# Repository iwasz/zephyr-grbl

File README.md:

# What this is
A GRBL ported to Zephyr RTOS with some additional features like software CDC ACM serial port and SD card support. Developed for my CoreXY pen ploter, so some features of GRBL are commented out. Please create an issue or propose a pull request if you are interested in more functionality (list of unsupported bits is below). The greatest benefit of having the GRBL ported to Zephyr is the ability of running it on variety of platforms with way more powerful CPUs than the original Arduino. As of now this project is targeting the [STM32F405RG](https://www.st.com/en/microcontrollers-microprocessors/stm32f405rg.html) (earlier tests were performed on the [STM32F446RE](https://www.st.com/en/microcontrollers-microprocessors/stm32f446re.html)) and with minor modifications in the *boards* directory or *overlay* file (or adding either of those to be precise) it should work on different STM32-s as well.

The only *non standard* driver this project uses is the `modules/hw_timer` and this is the only obstacle for running this on MCUs different than STM32-s. `modules/hw_timer` is derived from the `pwm` driver and its only purpose is to fire a callback(s) on a timer update event (and possibly on output compare event in the future). Other parts are implemented in stock Zephyr.

The project was written to power my [CoreXY pen plotter](https://hackaday.io/project/177237-corexy-pen-plotter), and as such has some parts not implemented (probing) and others not tested (Z-axis with stepper motor, see below). It should be a good starting point to develop something more complete that would run the variety of CNC machines. Pull requests are welcome.

* [TODO](TODO.md) list of things to do.
* [My notes](NOTES.md) on problems I've had.
* [Hackaday.io project page](https://hackaday.io/project/177237-corexy-pen-plotter)

# How to build
Tested with Zephyr RTOS 2.6.99. Familiarize yourself with the [Zephyr RTOS build process](https://docs.zephyrproject.org/latest/getting_started/index.html) first. :

## With bootloader
?

## Without bootloader (only for troubleshooting)
That is when `CONFIG_BOOTLOADER_MCUBOOT=n` in the `prj.conf`.
```sh
rm -Rf build
cmake -B build -GNinja -DBOARD=plotter_f405rg -DBOARD_ROOT=. .
ninja -C build
west flash # Or use IDE, or use openocd directly
```

## What has been done in order to port GRBL
* Added a new macro for my machine named DEFAULTS_ZEPHYR_GRBL_PLOTTER in the `config.h` and globally in the `CMakeLists.txt`. Used mostly in the `defaults.h`
* Coolant control, spindle **comented out**.
* [x] Added `extern "C" {` to most of the `*.h` files to enable C++ interoperability.
* [x] Added definitions for my machine in the `defaults.h`.
* [ ] Eeprom support ported.
* [x] Zephyr PWM module was modified to accept a timer output compare ISR callback.
* [x] AVR GPIO registers code ported to zephyr
* [x] Homing and limiters ported.
* [x] Probe implementation commented out.
* [x] Control switches support commented out. I'll have an OLED display and I can add those features there.
* [x] Spindle control commented out.
* [x] ~~Gpio inverting functionality stripped down as from now the Zephyr's device tree configuration is used for this.~~
* ~~Logging ported to Zephyr.~~ Rolled back.
* [x] Port uart code to zephyr.
  * [ ] ~~Make use of new async uart functionality merged recently to zephyr.~~ [Analogous to this](https://github.com/zephyrproject-rtos/zephyr/pull/30917/commits/a62711bd260fea80948f668d35b05452bd26e95f).
    * [x] ~~Modify the overlay.~~
    * [x] ~~Turn DMA on in Kconfig.~~
    * [x] Interrupt UART API and Zephyr ring buffers.
* GRBL seems to lack any call to a `delay` function in the main loop. This prevents scheduler from switching to other lower-priority threads which in my case were : `idle`, `logging` and `shell_uart`. I've lowered the main thread priority to 14 (from 0) and added k_yeld, so other low priority threads have a chance to run now. This include logging, shell and others.
-----
-----
-----

# Topics to mention in a write up
* Software
  * Out of tree driver for timer callback.
  * TMC driver?
  * GRBL obviously.

## Driver
Derived from PWM driver. Changes:

Header:
* Names (file names & all the names in the code). PWM -> HW_TIMER.
* A `typedef` for the callback.
* Few macro / defines.

Source file:
* Names
* Callback setter
* Datadield for the callback.
* TODO remove unused code.

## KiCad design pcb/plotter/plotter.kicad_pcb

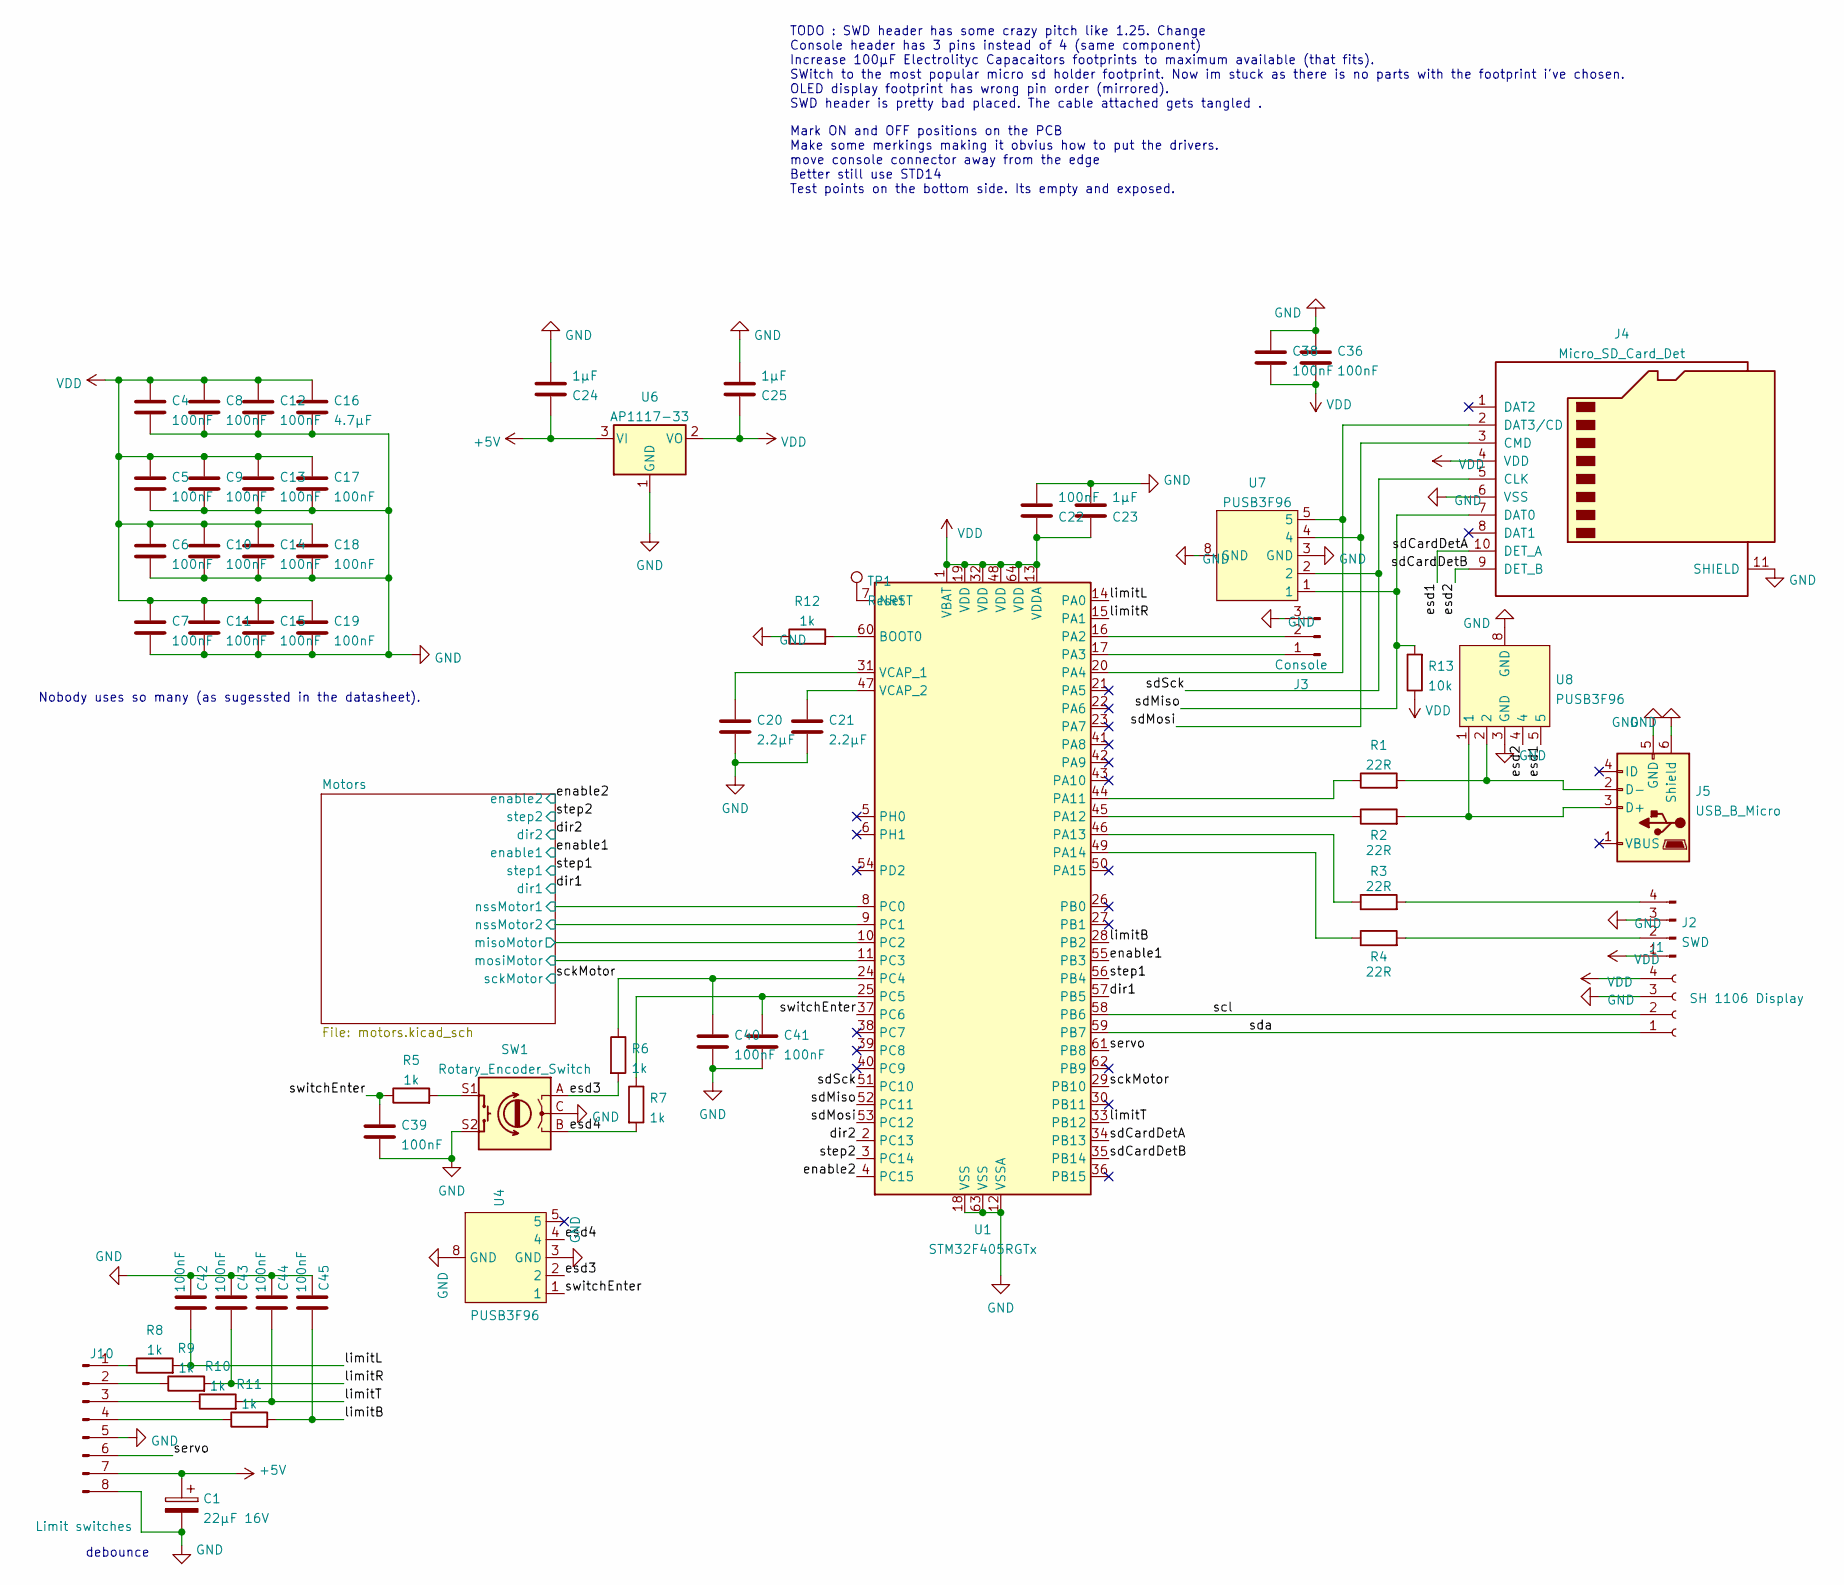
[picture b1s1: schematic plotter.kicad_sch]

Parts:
C1: 22µF 16V; CP_Elec_8x10
C4, C5, C6, C7, C8, C9, C10, C11, C12, C13, C14, C15, C17, C18, C19, C22, C36, C38, C39, C40, C41, C42, C43, C44, C45: 100nF; C_0603_1608Metric
C16: 4.7µF; C_1210_3225Metric
C20, C21: 2.2µF; C_1206_3216Metric
C23, C24, C25: 1µF; C_0603_1608Metric
J1: SH 1106 Display; SH1106
J2: SWD; PinHeader_1x04_P1.27mm_Vertical
J3: Console; PinHeader_1x03_P1.27mm_Vertical
J4: Micro_SD_Card_Det; microSD_HC_Hirose_DM3AT-SF-PEJM5
J5: USB_B_Micro; USB_Micro-B_Amphenol_10104110_Horizontal
J10: Limit switches; JST_PH_B8B-PH-K_1x08_P2.00mm_Vertical
R1, R2, R3, R4: 22R; R_0603_1608Metric
R5, R6, R7, R8, R9, R10, R11, R12: 1k; R_0603_1608Metric
R13: 10k; R_0603_1608Metric
SW1: Rotary_Encoder_Switch; RotaryEncoder_Alps_EC11E_Vertical_H20mm
TP1: Reset; TestPoint_Pad_1.5x1.5mm
U1: STM32F405RGTx; LQFP-64_10x10mm_P0.5mm
U4, U7, U8: PUSB3F96; Diodes_UDFN-10_1.0x2.5mm_P0.5mm
U6: AP1117-33; SOT-223-3_TabPin2

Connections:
+5V: C1.1, C24.1, J10.7, U6.3 (VI); also elsewhere on the board
/Motors/misoMotor: U1.10 (PC2); also elsewhere on the board
/Motors/mosiMotor: U1.11 (PC3); also elsewhere on the board
/Motors/nssMotor1: U1.8 (PC0); also elsewhere on the board
/Motors/nssMotor2: U1.9 (PC1); also elsewhere on the board
/dir1: U1.57 (PB5); also elsewhere on the board
/dir2: U1.2 (PC13); also elsewhere on the board
/enable1: U1.55 (PB3); also elsewhere on the board
/enable2: U1.4 (PC15); also elsewhere on the board
/esd1: J4.10 (DET_A), U1.34 (PB13), U8.5
/esd2: J4.9 (DET_B), U1.35 (PB14), U8.4
/esd3: R6.2, SW1.A, U4.2
/esd4: R7.2, SW1.B, U4.4
/limitB: C45.2, R11.2, U1.28 (PB2)
/limitL: C42.2, R8.2, U1.14 (PA0)
/limitR: C43.2, R9.2, U1.15 (PA1)
/limitT: C44.2, R10.2, U1.33 (PB12)
/sckMotor: U1.29 (PB10); also elsewhere on the board
/scl: J1.2, U1.58 (PB6)
/sdMiso: J4.7 (DAT0), R13.2, U1.52 (PC11), U7.1
/sdMosi: J4.3 (CMD), U1.53 (PC12), U7.4
/sdSck: J4.5 (CLK), U1.51 (PC10), U7.2
/sda: J1.1, U1.59 (PB7)
/servo: J10.6, U1.61 (PB8)
/step1: U1.56 (PB4); also elsewhere on the board
/step2: U1.3 (PC14); also elsewhere on the board
/switchEnter: C39.1, R5.1, U1.37 (PC6), U4.1
GND: C1.2, C4.2, C5.2, C6.2, C7.2, C8.2, C9.2, C10.2, C11.2, C12.2, C13.2, C14.2, C15.2, C16.2, C17.2, C18.2, C19.2, C20.2, C21.2, C22.2, C23.2, C24.2, C25.2, C36.1, C38.1, C39.2, C40.2, C41.2, C42.1, C43.1, C44.1, C45.1, J1.3, J2.3, J3.3, J4.6 (VSS), J4.11 (SHIELD), J5.5 (GND), J5.6 (Shield), J10.5, J10.8, R12.1, SW1.C, SW1.S2, U1.12 (VSSA), U1.18 (VSS), U1.63 (VSS), U4.3 (GND), U4.8 (GND), U6.1 (GND), U7.3 (GND), U7.8 (GND), U8.3 (GND), U8.8 (GND); also elsewhere on the board
unnamed: C20.1, U1.31 (VCAP_1)
unnamed: C21.1, U1.47 (VCAP_2)
unnamed: C40.1, R6.1, U1.24 (PC4)
unnamed: C41.1, R7.1, U1.25 (PC5)
unnamed: J2.2, R4.2
unnamed: J2.4, R3.2
unnamed: J3.1, U1.17 (PA3)
unnamed: J3.2, U1.16 (PA2)
unnamed: J4.2 (DAT3/CD), U1.20 (PA4), U7.5
unnamed: J5.2 (D-), R1.2, U8.2
unnamed: J5.3 (D+), R2.2, U8.1
unnamed: J10.1, R8.1
unnamed: J10.2, R9.1
unnamed: J10.3, R10.1
unnamed: J10.4, R11.1
unnamed: R1.1, U1.44 (PA11)
unnamed: R2.1, U1.45 (PA12)
unnamed: R3.1, U1.46 (PA13)
unnamed: R4.1, U1.49 (PA14)
unnamed: R5.2, SW1.S1
unnamed: R12.2, U1.60 (BOOT0)
unnamed: TP1.1, U1.7 (NRST)
VDD: C4.1, C5.1, C6.1, C7.1, C8.1, C9.1, C10.1, C11.1, C12.1, C13.1, C14.1, C15.1, C16.1, C17.1, C18.1, C19.1, C22.1, C23.1, C25.1, C36.2, C38.2, J1.4, J2.1, J4.4 (VDD), R13.1, U1.1 (VBAT), U1.13 (VDDA), U1.19 (VDD), U1.32 (VDD), U1.48 (VDD), U1.64 (VDD), U6.2 (VO)

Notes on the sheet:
Nobody uses so many (as sugessted in the datasheet).
TODO : SWD header has some crazy pitch like 1.25. Change Console header has 3 pins instead of 4 (same component) Increase 100µF Electrolityc Capacaitors footprints to maximum available (that fits). SWitch to the most popular micro sd holder footprint. Now im stuck as there is no parts with the foot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
Mark ON and OFF positions on the PCB Make some merkings making it obvius how to put the drivers. move console connector away from the edge Better still use STD14 Test points on the bottom side. Its empty and exposed.
debounce

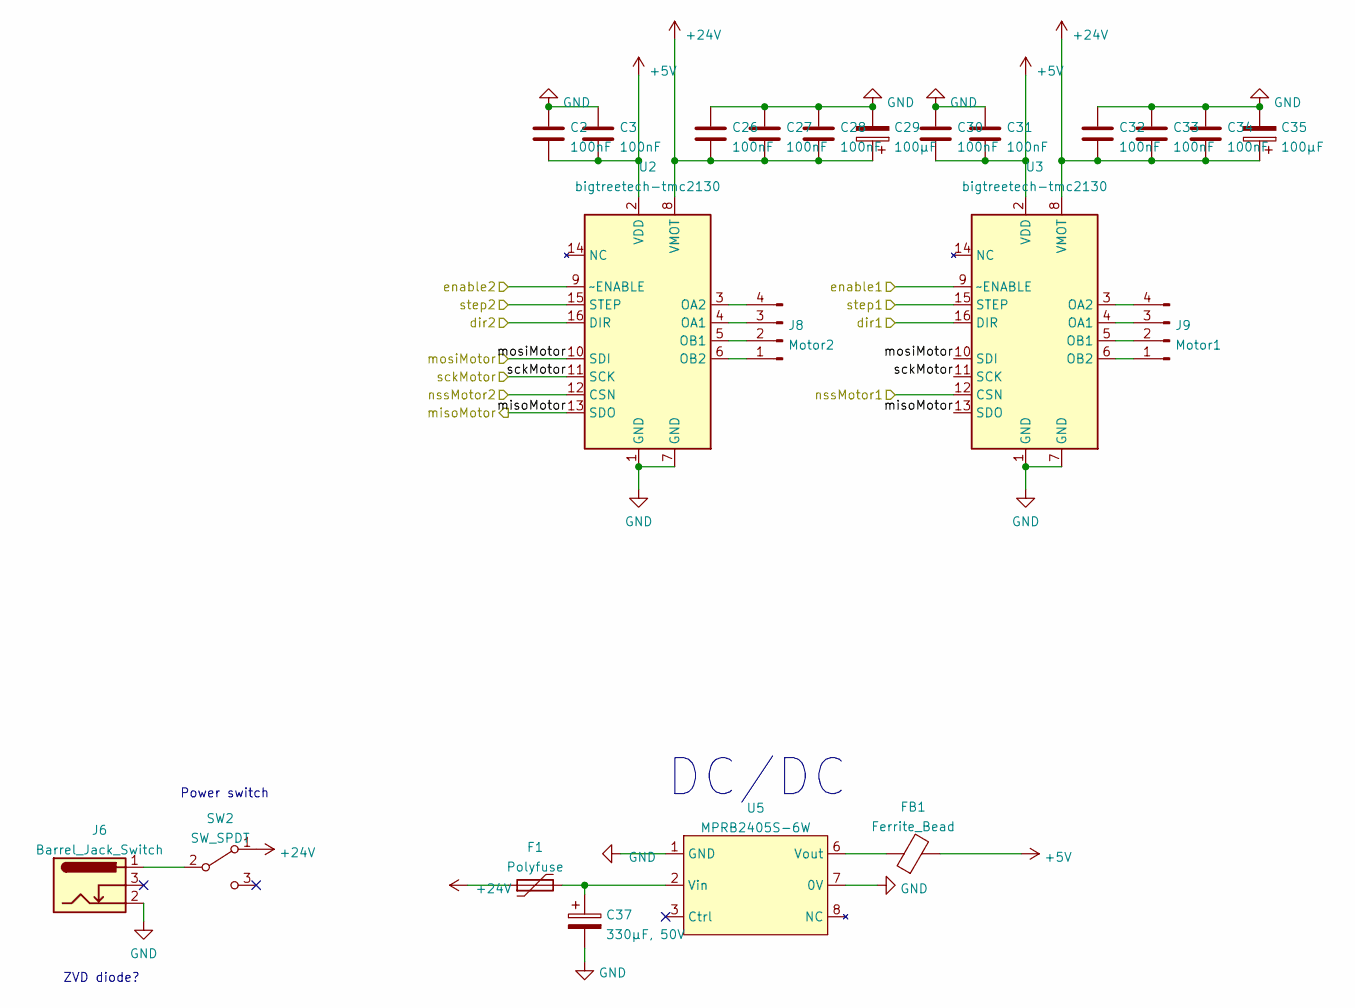
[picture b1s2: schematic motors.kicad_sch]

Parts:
C2, C3, C26, C27, C28, C30, C31, C32, C33, C34: 100nF; C_0603_1608Metric
C29, C35: 100µF; CP_Elec_8x10
C37: 330µF, 50V; CP_Elec_8x10
F1: Polyfuse; Fuse_1812_4532Metric
FB1: Ferrite_Bead; L_0603_1608Metric
J6: Barrel_Jack_Switch; BarrelJack_Horizontal
J8: Motor2; JST_PH_B4B-PH-K_1x04_P2.00mm_Vertical
J9: Motor1; JST_PH_B4B-PH-K_1x04_P2.00mm_Vertical
SW2: SW_SPDT; MFP 201 NR_copy
U2, U3: bigtreetech-tmc2130; Pololu_Breakout-16_15.2x20.3mm
U5: MPRB2405S-6W

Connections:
+5V: C2.2, C3.2, C30.2, C31.2, FB1.2, U2.2 (VDD), U3.2 (VDD); also elsewhere on the board
+24V: C26.2, C27.2, C28.2, C29.1, C32.2, C33.2, C34.2, C35.1, F1.1, SW2.1 (A), U2.8 (VMOT), U3.8 (VMOT)
/Motors/misoMotor: U2.13 (SDO), U3.13 (SDO); also elsewhere on the board
/Motors/mosiMotor: U2.10 (SDI), U3.10 (SDI); also elsewhere on the board
/Motors/nssMotor1: U3.12 (CSN); also elsewhere on the board
/Motors/nssMotor2: U2.12 (CSN); also elsewhere on the board
/dir1: U3.16 (DIR); also elsewhere on the board
/dir2: U2.16 (DIR); also elsewhere on the board
/enable1: U3.9 (~ENABLE); also elsewhere on the board
/enable2: U2.9 (~ENABLE); also elsewhere on the board
/sckMotor: U2.11 (SCK), U3.11 (SCK); also elsewhere on the board
/step1: U3.15 (STEP); also elsewhere on the board
/step2: U2.15 (STEP); also elsewhere on the board
GND: C2.1, C3.1, C26.1, C27.1, C28.1, C29.2, C30.1, C31.1, C32.1, C33.1, C34.1, C35.2, C37.2, J6.2, U2.1 (GND), U2.7 (GND), U3.1 (GND), U3.7 (GND), U5.1 (GND), U5.7 (0V); also elsewhere on the board
unnamed: C37.1, F1.2, U5.2 (Vin)
unnamed: FB1.1, U5.6 (Vout)
unnamed: J6.1, SW2.2 (B)
unnamed: J8.1, U2.6 (OB2)
unnamed: J8.2, U2.5 (OB1)
unnamed: J8.3, U2.4 (OA1)
unnamed: J8.4, U2.3 (OA2)
unnamed: J9.1, U3.6 (OB2)
unnamed: J9.2, U3.5 (OB1)
unnamed: J9.3, U3.4 (OA1)
unnamed: J9.4, U3.3 (OA2)

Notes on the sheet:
DC/DC
Power switch
ZVD diode?

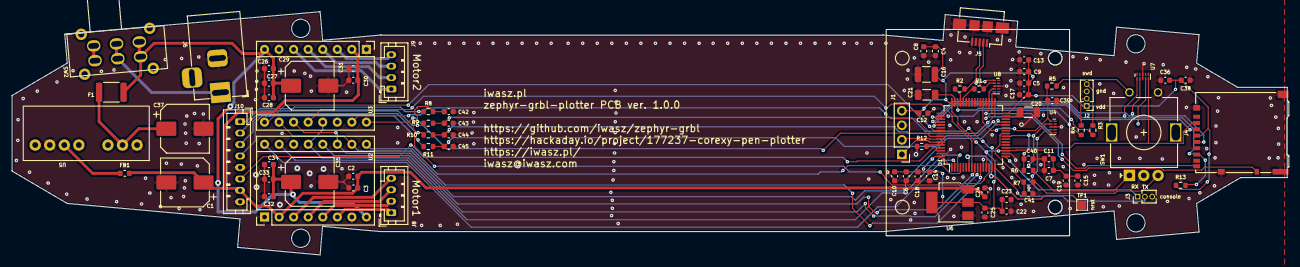
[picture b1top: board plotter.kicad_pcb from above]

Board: 2 copper layers, 222.6 x 42.4 mm, 80 parts (0 on the bottom side), 63 nets.

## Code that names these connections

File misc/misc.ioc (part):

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Mcu.Name=STM32F405RGTx
Mcu.Package=LQFP64
Mcu.UserName=STM32F405RGTx
PA0-WKUP.Signal=GPIO_Input
PA1.Signal=GPIO_Input
PA11.Mode=Device_Only
PA11.Signal=USB_OTG_FS_DM
PA12.Mode=Device_Only
PA12.Signal=USB_OTG_FS_DP
PA13.Mode=Serial_Wire
PA13.Signal=SYS_JTMS-SWDIO
PA14.Mode=Serial_Wire
PA14.Signal=SYS_JTCK-SWCLK
PA2.Mode=Asynchronous
PA2.Signal=USART2_TX
PA3.Mode=Asynchronous
PA3.Signal=USART2_RX
PA4.Mode=NSS_Signal_Hard_Output
PA4.Signal=SPI1_NSS
PA5.Mode=Full_Duplex_Master
PA5.Signal=SPI1_SCK
PA6.Mode=Full_Duplex_Master
PA6.Signal=SPI1_MISO
PA7.Mode=Full_Duplex_Master
PA7.Signal=SPI1_MOSI
PB10.Mode=Full_Duplex_Master
PB10.Signal=SPI2_SCK
PB11.Signal=GPIO_Output
PB12.Signal=GPIO_Input
PB13.Signal=GPIO_Input
PB14.Signal=GPIO_Input
PB2.Signal=GPIO_Input
PB3.Signal=GPIO_Output
PB4.Signal=GPIO_Output
PB5.Signal=GPIO_Output
PB6.Mode=I2C
PB6.Signal=I2C1_SCL
PB7.Mode=I2C
PB7.Signal=I2C1_SDA
PB8.Signal=S_TIM4_CH3
PC0.Signal=GPIO_Input
PC1.Signal=GPIO_Output
PC10.Mode=Full_Duplex_Master
PC10.Signal=SPI3_SCK
PC11.Mode=Full_Duplex_Master
PC11.Signal=SPI3_MISO
PC12.Mode=Full_Duplex_Master
PC12.Signal=SPI3_MOSI
PC13-ANTI_TAMP.Signal=GPIO_Output
PC14-OSC32_IN.Signal=GPIO_Output
PC15-OSC32_OUT.Signal=GPIO_Output
PC2.Mode=Full_Duplex_Master
PC2.Signal=SPI2_MISO
PC3.Mode=Full_Duplex_Master
PC3.Signal=SPI2_MOSI
PC4.Signal=GPIO_Input
PC5.Signal=GPIO_Input
PC6.Signal=GPIO_Input
RCC.HSE_VALUE=25000000
RCC.SYSCLKFreq_VALUE=168000000
RCC.SYSCLKSource=RCC_SYSCLKSOURCE_PLLCLK
board=custom

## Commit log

2020-11-12 First motor movement
2020-11-13 I integrated my project with TMC 2130 library instead of fighting with its registers manuallyu, and from the start it performs way better than what was before.
2020-11-16 Both motors work, plotter moves both ways.
2020-11-24 Nucleo 743 support, because I fried the discovery board (and one TMC driver at the same time).
2020-11-24 SDHC test, simple example works great
2020-12-09 Works with hardware timer
2020-12-09 Refactor
2021-01-18 Test movements.
2021-01-18 Stepper.c compiles
2021-01-20 UART IRQ mode
2021-01-20 Switched back to H7 when I discovered, that no DMA is necessary.
2021-08-19 Switch to F446re. Compiles, hangs on USART3 comms.
2021-08-20 Works (moves in random some direction) with UGS's jog controller as previously.
2021-08-31 The machine seems to understand a simple gcode (circle) but only if the firmware was compiled with O2.
2021-09-01 CDC-ACM work in progress.
2021-09-01 Console restored, CubeMX project file added and inactive (commented) code removed.
2021-09-01 Stack overflows when -O0 sorted out.
2021-09-02 Zephyr ring buffers used along with the CDC ACM USB class. In this commit the Zephyr console prints on the usual USB2, and GRBL communicates through the CDC ACM.
2021-09-02 Logging restored
2021-09-03 Priority of the main thread lowered to 14, and k_yeld added in the GRBL.
2021-09-03 Critical sections with IRQ barriers. UGS seems to cooperate perfectly now. At least the circle works.
2021-09-07 Z axis, and some examples. Still work in progress, but at this point it draws rather nicely.
2021-09-08 Feed rate and AMASS
2021-09-08 Minor changes
2021-09-08 32 bit timer used for generating stepper pulses.
2021-09-09 Sphere.ngc example corrected according to new, fixed feed rates.
2021-09-10 Testing procedure and TMC settings copied from the Prusa firmware.
2021-09-10 Submodule
2021-09-10 Cleanup of GRBL modifications - I"m incorporating the gnea/grbl into this repo, and making the modifications once again
2021-09-10 Grbl directory is now included in this repo instead of beeing a submodule.
2021-09-10 Limit switches work in progress.
2021-09-14 Limit switches and homing.
2021-09-14 Directory name change : grbl2 -> gnea-grbl
2021-09-14 Work in progress on the NVS (in flash) aka eeprom implementation. Does not work yet.
2021-09-16 Work started on the PCB.
2021-09-17 Moving to STM32F405 and the final pinout (as on the PCB in the future).
2021-09-17 Readme
2021-09-17 F405 Works OK.
2021-09-17 Threads WIP
2021-09-20 PCB and 3d model. Still work in progress.
2021-09-21 Thread priorites.
2021-09-21 OCnflict resolved (after merge)
2021-09-21 Max feed rate increased to 15000mm/min. But the scale of the distances traveled is wrong. Instead of 10cm it goes like 15-20.
2021-09-23 Work on the SD cared impl.
2021-09-23 SD card subsystem intercepts the GRBL comms nicely.
2021-09-24 Communication with the GRBL for SD card impl.
2021-09-25 Encoder.
2021-09-25 Jojs -0.5mm when encoder pressed (encoder with a button).
2021-09-27 Working state, but a little bit unstable at a times.
2021-09-27 Encoder, and jogging.
2021-09-27 Encoder and jogging.
2021-09-28 Basic menu on the OLED
2021-09-28 Encoder. Debuncing. Best so far, but not quite
2021-09-29 Encoder done better.
2021-09-29 Encoder OK.
2021-10-05 I finally got the SD card to work.
2021-10-17 Bringing up the first PCB
2021-10-20 Schematics minor changes
2021-10-26 FreeCad files mod
2021-10-27 3d model work
2021-11-13 3d model changes mostly
2021-11-13 Directions corrected.
2023-06-25 Compatibility with zephyr 3.4.99
2023-06-25 Undefined initialization levels used problem resolved
2023-07-03 Steppers config upudated
2023-07-04 OLED screen initialization problem fixed
